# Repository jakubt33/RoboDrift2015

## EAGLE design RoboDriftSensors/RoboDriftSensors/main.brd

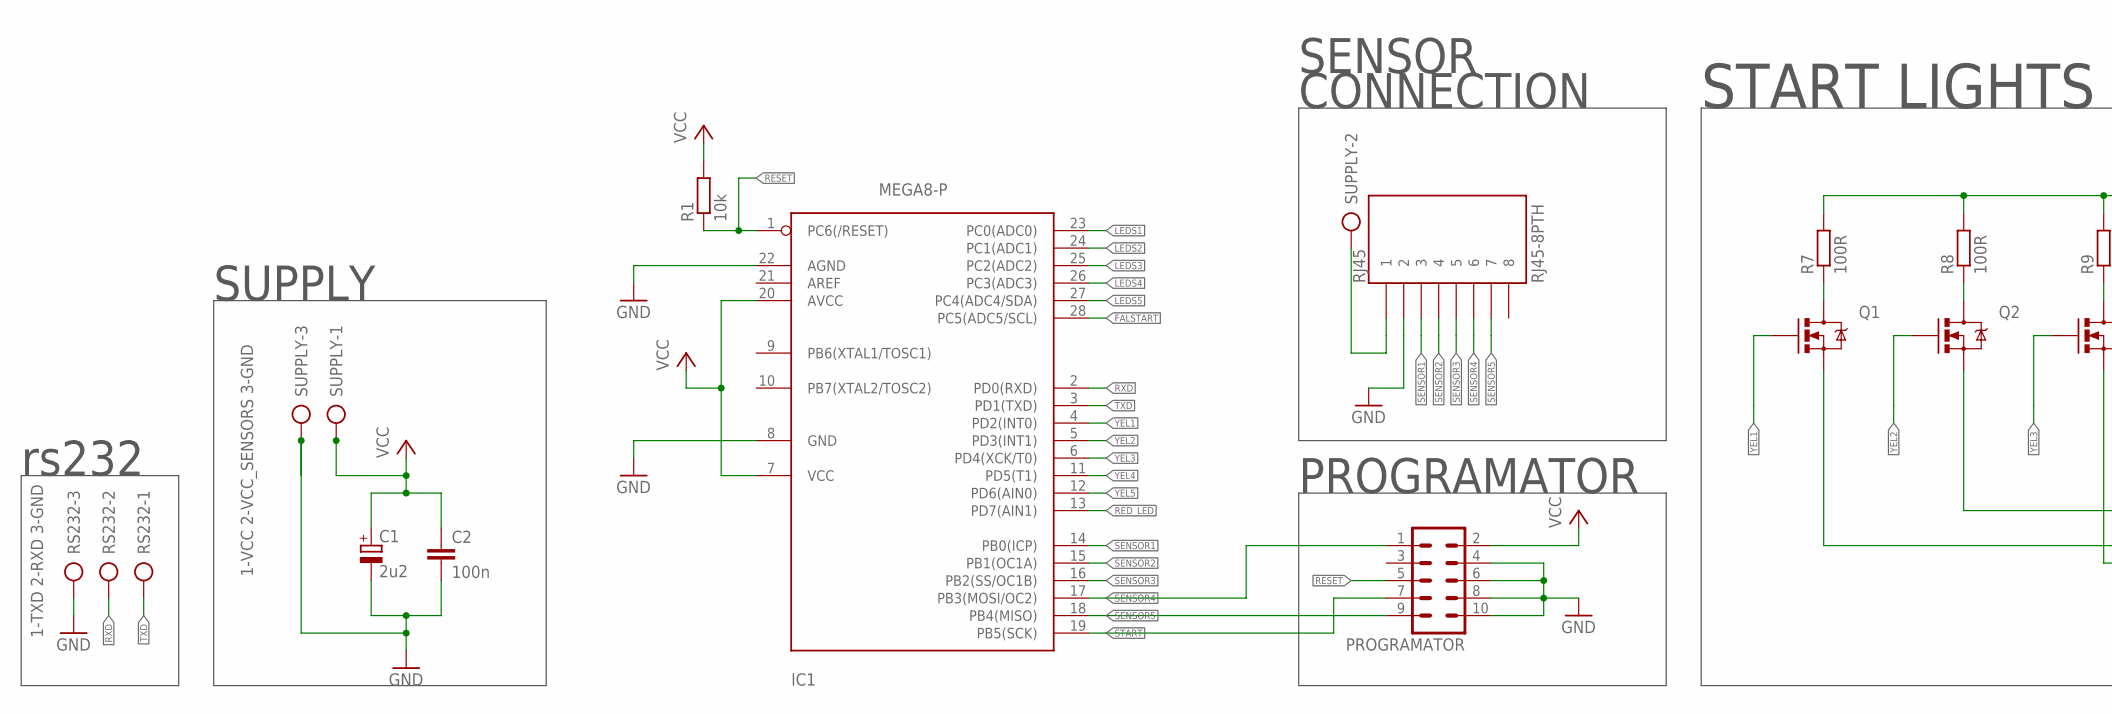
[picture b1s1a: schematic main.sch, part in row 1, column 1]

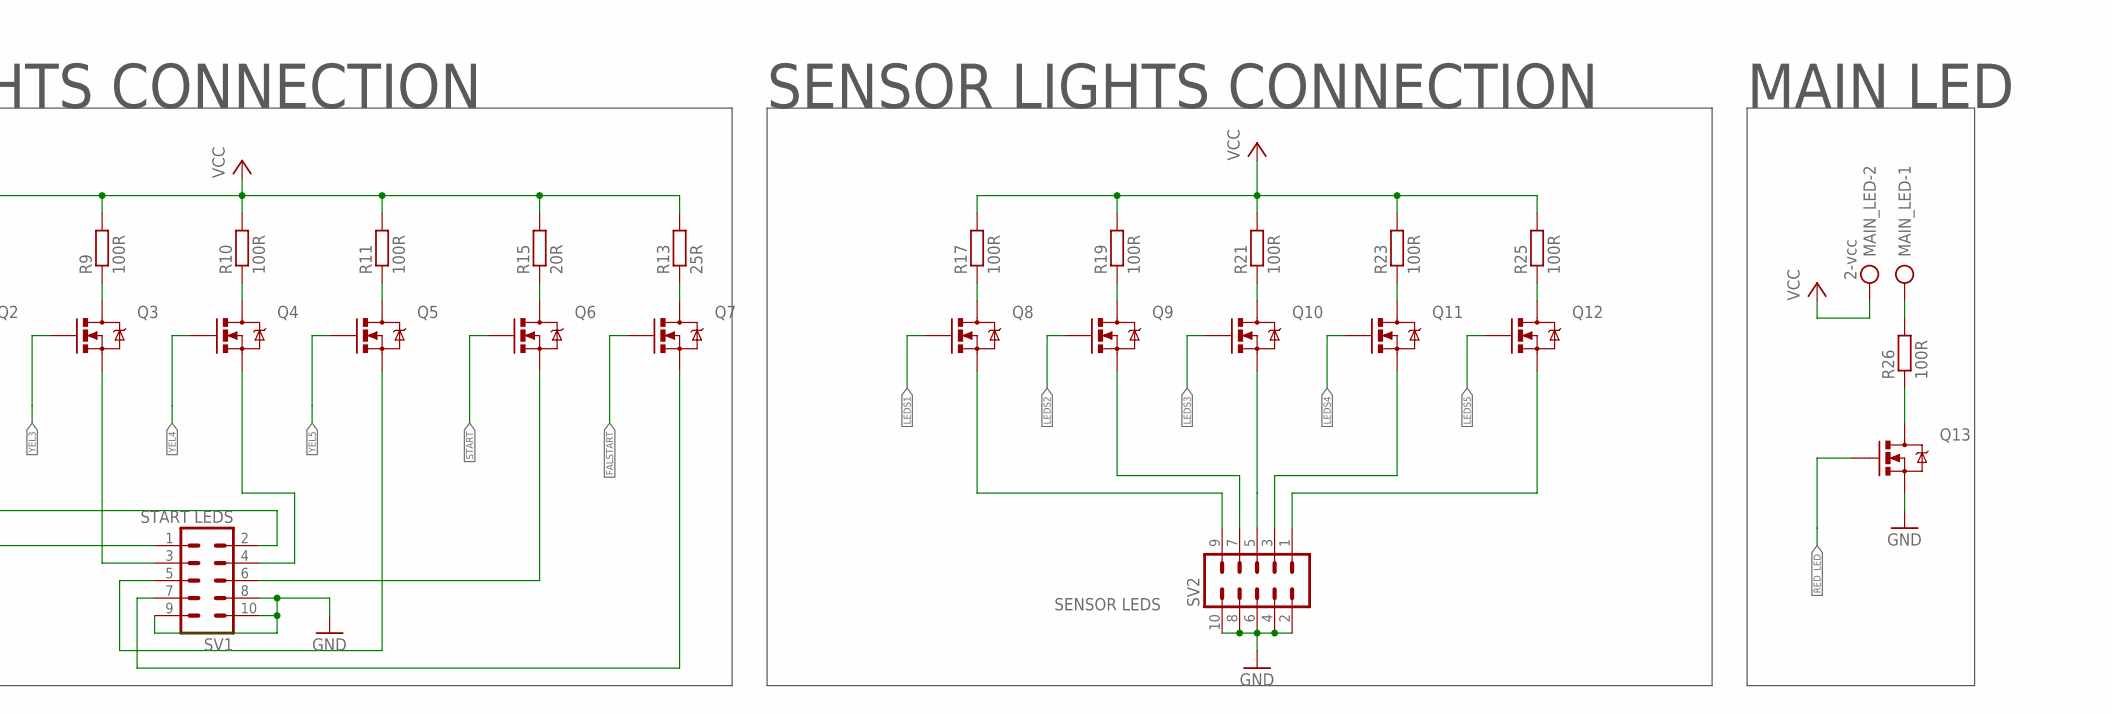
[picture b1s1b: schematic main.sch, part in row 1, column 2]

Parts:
C1: 2u2; E2-5
C2: 100n; C0805
IC1: MEGA8-P; DIL28-3
MAIN_LED: 2-vcc; AK300/2
PROGRAMATOR: ML10L
Q1, Q2, Q3, Q4, Q5, Q6, Q7, Q8, Q9, Q10, Q11, Q12, Q13: MOSFET-NCHANNEL2N7002PW; SOT323
R1: 10k; R0805
R7, R8, R9, R10, R11, R17, R19, R21, R23, R25, R26: 100R; R0805
R13: 25R; R0805
R15: 20R; R0805
RJ45: RJ45-8PTH; RJ45-8
RS232: 1-TXD 2-RXD 3-GND; AK300/3
SUPPLY: 1-VCC 2-VCC_SENSORS 3-GND; AK300/3
SV1: START LEDS; ML10
SV2: SENSOR LEDS; ML10

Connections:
FALSTART: IC1.28 (PC5(ADC5/SCL)), Q7.1 (G)
GND: C1.-, C2.2, IC1.8 (GND), IC1.22 (AGND), PROGRAMATOR.4, PROGRAMATOR.6, PROGRAMATOR.8, PROGRAMATOR.10, Q13.2 (S), RJ45.2, RS232.3, SUPPLY.3, SV1.8, SV1.9, SV1.10, SV2.2, SV2.4, SV2.6, SV2.8, SV2.10
LEDS1: IC1.23 (PC0(ADC0)), Q8.1 (G)
LEDS2: IC1.24 (PC1(ADC1)), Q9.1 (G)
LEDS3: IC1.25 (PC2(ADC2)), Q10.1 (G)
LEDS4: IC1.26 (PC3(ADC3)), Q11.1 (G)
LEDS5: IC1.27 (PC4(ADC4/SDA)), Q12.1 (G)
unnamed: Q1.3 (D), R7.1
unnamed: Q8.2 (S), SV2.9
unnamed: Q2.3 (D), R8.1
unnamed: Q3.3 (D), R9.1
unnamed: Q4.3 (D), R10.1
unnamed: Q5.3 (D), R11.1
unnamed: Q9.2 (S), SV2.7
unnamed: Q11.2 (S), SV2.3
unnamed: Q12.2 (S), SV2.1
unnamed: Q7.3 (D), R13.1
unnamed: Q6.3 (D), R15.1
unnamed: Q8.3 (D), R17.1
unnamed: Q9.3 (D), R19.1
unnamed: Q10.3 (D), R21.1
unnamed: Q11.3 (D), R23.1
unnamed: Q12.3 (D), R25.1
unnamed: Q10.2 (S), SV2.5
unnamed: Q1.2 (S), SV1.1
unnamed: Q2.2 (S), SV1.2
unnamed: Q3.2 (S), SV1.3
unnamed: Q4.2 (S), SV1.4
unnamed: Q5.2 (S), SV1.5
unnamed: Q6.2 (S), SV1.6
unnamed: Q7.2 (S), SV1.7
unnamed: RJ45.1, SUPPLY.2
unnamed: Q13.3 (D), R26.1
unnamed: MAIN_LED.1, R26.2
RED_LED: IC1.13 (PD7(AIN1)), Q13.1 (G)
RESET: IC1.1 (PC6(/RESET)), PROGRAMATOR.5, R1.1
RXD: IC1.2 (PD0(RXD)), RS232.2
SENSOR1: IC1.14 (PB0(ICP)), RJ45.3
SENSOR2: IC1.15 (PB1(OC1A)), RJ45.4
SENSOR3: IC1.16 (PB2(SS/OC1B)), RJ45.5
SENSOR4: IC1.17 (PB3(MOSI/OC2)), PROGRAMATOR.1, RJ45.6
SENSOR5: IC1.18 (PB4(MISO)), PROGRAMATOR.9, RJ45.7
START: IC1.19 (PB5(SCK)), PROGRAMATOR.7, Q6.1 (G)
TXD: IC1.3 (PD1(TXD)), RS232.1
VCC: C1.+, C2.1, IC1.7 (VCC), IC1.20 (AVCC), MAIN_LED.2, PROGRAMATOR.2, R1.2, R7.2, R8.2, R9.2, R10.2, R11.2, R13.2, R15.2, R17.2, R19.2, R21.2, R23.2, R25.2, SUPPLY.1
YEL1: IC1.4 (PD2(INT0)), Q1.1 (G)
YEL2: IC1.5 (PD3(INT1)), Q2.1 (G)
YEL3: IC1.6 (PD4(XCK/T0)), Q3.1 (G)
YEL4: IC1.11 (PD5(T1)), Q4.1 (G)
YEL5: IC1.12 (PD6(AIN0)), Q5.1 (G)

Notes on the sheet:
START LIGHTS CONNECTION
SENSOR LIGHTS CONNECTION
PROGRAMATOR
SUPPLY
rs232
MAIN LED
CONNECTION
SENSOR

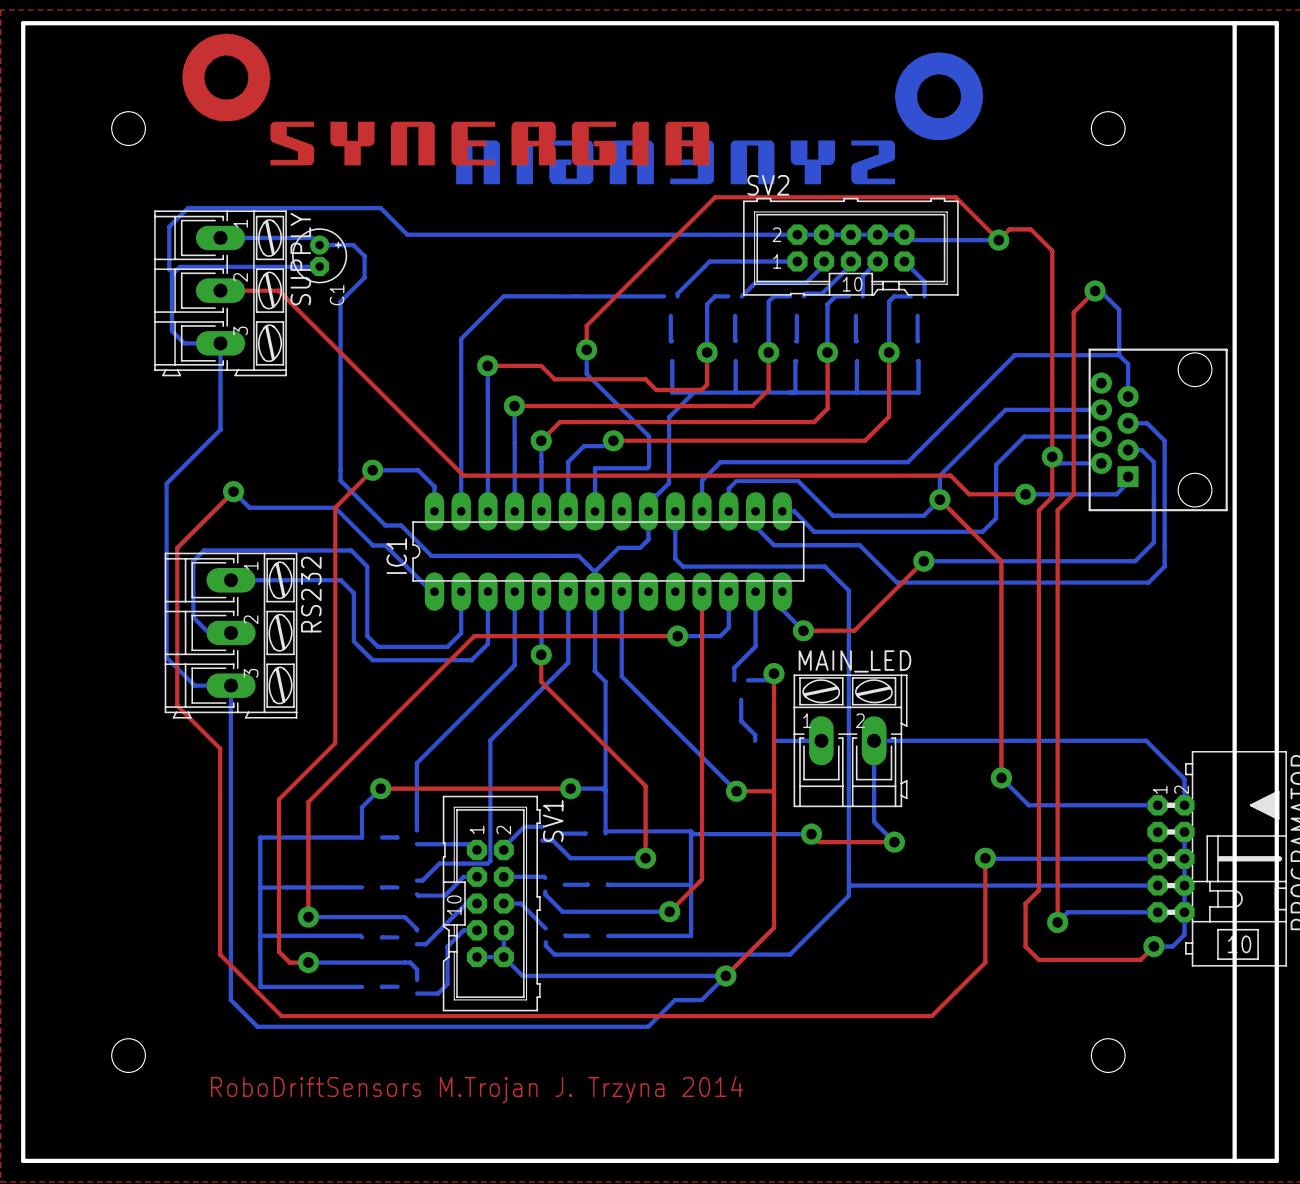
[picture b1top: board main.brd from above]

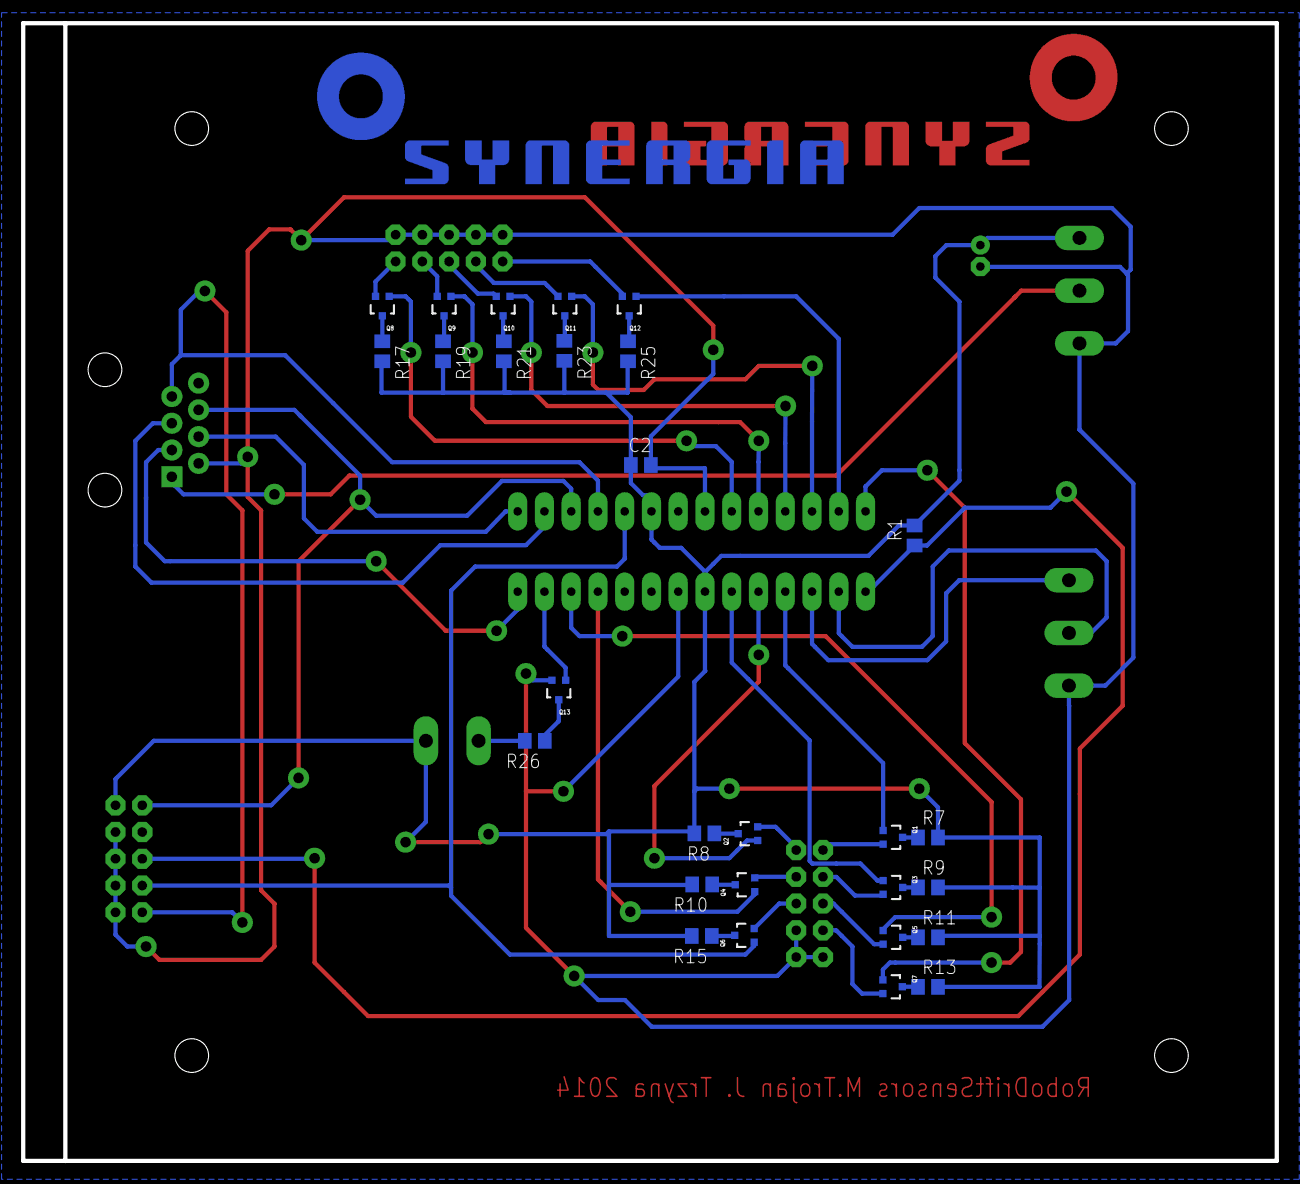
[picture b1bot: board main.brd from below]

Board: 2 copper layers, 119.0 x 108.0 mm, 39 parts (29 on the bottom side), 50 nets.

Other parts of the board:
U$1, U$2: SYNERGIA_50MM

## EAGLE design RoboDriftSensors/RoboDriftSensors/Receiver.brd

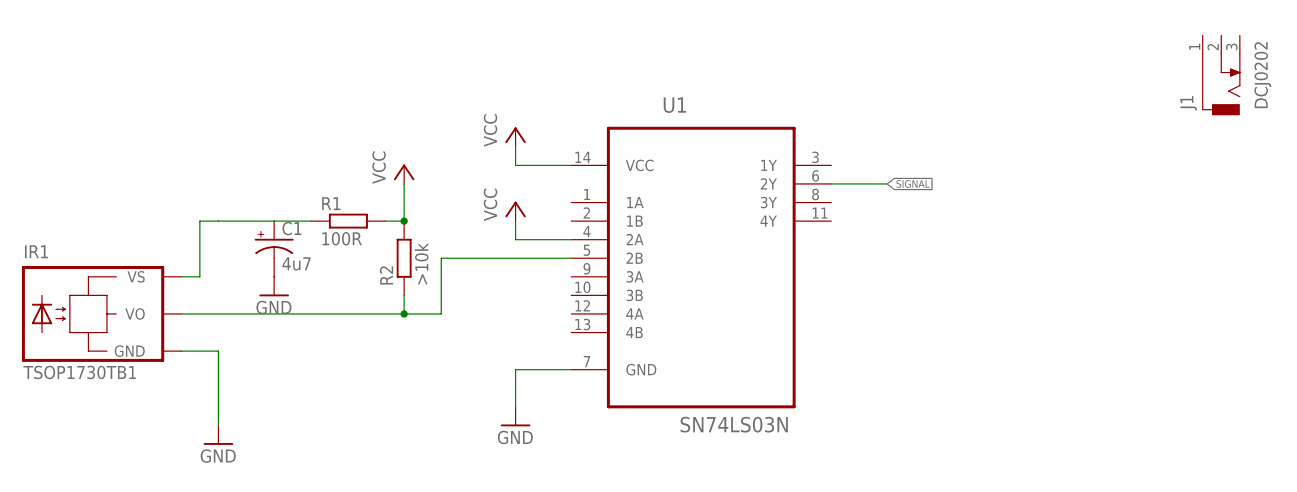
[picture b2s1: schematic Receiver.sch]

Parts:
C1: 4u7; E2-4
IR1: TSOP1730TB1; TSOP17_TB1
J1: DCJ0202
R1: 100R; 0204/5
R2: >10k; 0204/5
U1: SN74LS03N; DIP254P762X508-14

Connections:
GND: C1.-, IR1.GND, U1.7 (GND)
unnamed: IR1.VO, R2.1, U1.5 (2B)
unnamed: C1.+, IR1.VS, R1.1
SIGNAL: U1.6 (2Y)
VCC: R1.2, R2.2, U1.4 (2A), U1.14 (VCC)

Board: 2 copper layers, 6 parts (0 on the bottom side), 4 nets, no tracks yet.

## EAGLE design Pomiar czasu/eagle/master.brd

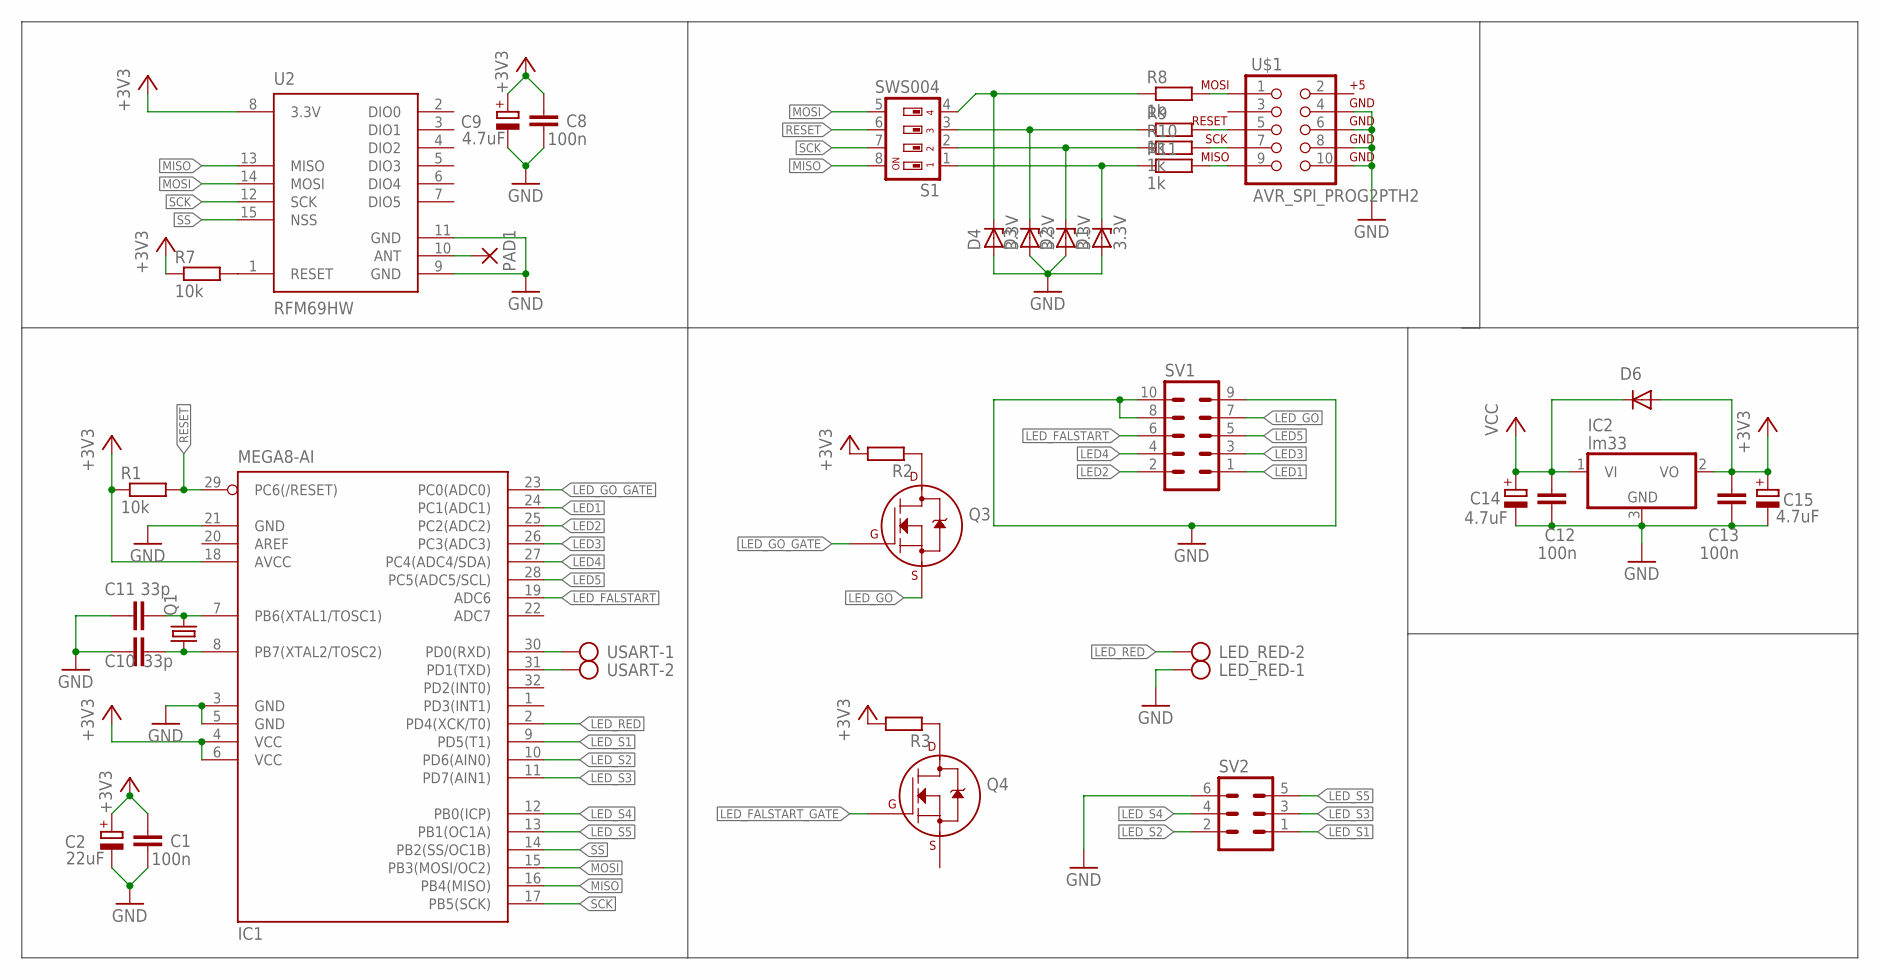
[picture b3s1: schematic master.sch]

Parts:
C1, C8, C12, C13: 100n; C0805
C2: 22uF; E2-5
C9, C14, C15: 4.7uF; E2-5
C10, C11: 33p; C0805
D1, D2, D3, D4: 3.3V; SOD80C
D6: DIODE-DO214AC; DO214AC
IC1: MEGA8-AI; TQFP32-08
IC2: lm33; TO252
LED_RED: AK500/2
PAD1: WIREPADSMD5-2,5; 5-2,5
Q1: CRYSTALHC49UP; HC49UP
Q3, Q4: 2N7000_SOT23; SOT-23
R1, R7: 10k; R0805
R2, R3: R-EU_R0805; R0805
R8, R9, R10, R11: 1k; R0805
S1: SWS004; SMS-004
SV1: ML10
SV2: ML6
U2: RFM69HW; RFM69W-XXXS2
U$1: AVR_SPI_PROG2PTH2; 2X5-SHROUDED
USART: AK500/2

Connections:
+3V3: C1.1, C2.+, C8.1, C9.+, C13.1, C15.+, D6.A, IC1.4 (VCC), IC1.6 (VCC), IC1.18 (AVCC), IC2.2 (VO), R1.1, R2.2, R3.2, R7.1, U2.8 (3.3V)
GND: C1.2, C2.-, C8.2, C9.-, C10.1, C11.1, C12.2, C13.2, C14.-, C15.-, D1.A, D2.A, D3.A, D4.A, IC1.3 (GND), IC1.5 (GND), IC1.21 (GND), IC2.3 (GND), LED_RED.1, SV1.8, SV1.9, SV1.10, SV2.6, U2.9 (GND), U2.11 (GND), U$1.4, U$1.6, U$1.8, U$1.10
LED1: IC1.24 (PC1(ADC1)), SV1.1
LED2: IC1.25 (PC2(ADC2)), SV1.2
LED3: IC1.26 (PC3(ADC3)), SV1.3
LED4: IC1.27 (PC4(ADC4/SDA)), SV1.4
LED5: IC1.28 (PC5(ADC5/SCL)), SV1.5
LED_FALSTART: IC1.19 (ADC6), SV1.6
LED_FALSTART_GATE: Q4.1 (G)
LED_GO: Q3.2 (S), SV1.7
LED_GO_GATE: IC1.23 (PC0(ADC0)), Q3.1 (G)
LED_RED: IC1.2 (PD4(XCK/T0)), LED_RED.2
LED_S1: IC1.9 (PD5(T1)), SV2.1
LED_S2: IC1.10 (PD6(AIN0)), SV2.2
LED_S3: IC1.11 (PD7(AIN1)), SV2.3
LED_S4: IC1.12 (PB0(ICP)), SV2.4
LED_S5: IC1.13 (PB1(OC1A)), SV2.5
MISO: IC1.16 (PB4(MISO)), S1.8, U2.13 (MISO)
MOSI: IC1.15 (PB3(MOSI/OC2)), S1.5, U2.14 (MOSI)
unnamed: Q3.3 (D), R2.1
unnamed: Q4.3 (D), R3.1
unnamed: R7.2, U2.1 (RESET)
unnamed: D4.C, R8.1, S1.4
unnamed: PAD1.1, U2.10 (ANT)
unnamed: D3.C, R9.1, S1.3
unnamed: D2.C, R10.1, S1.2
unnamed: D1.C, R11.1, S1.1
unnamed: R8.2, U$1.1
unnamed: R11.2, U$1.9
unnamed: R10.2, U$1.7
unnamed: R9.2, U$1.5
unnamed: C11.2, IC1.7 (PB6(XTAL1/TOSC1)), Q1.2
unnamed: C10.2, IC1.8 (PB7(XTAL2/TOSC2)), Q1.1
RESET: IC1.29 (PC6(/RESET)), R1.2, S1.6
RXD: IC1.30 (PD0(RXD)), USART.1
SCK: IC1.17 (PB5(SCK)), S1.7, U2.12 (SCK)
SS: IC1.14 (PB2(SS/OC1B)), U2.15 (NSS)
TXD: IC1.31 (PD1(TXD)), USART.2
VCC: C12.1, C14.+, D6.C, IC2.1 (VI)

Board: 2 copper layers, 36 parts (0 on the bottom side), 38 nets, no tracks yet.

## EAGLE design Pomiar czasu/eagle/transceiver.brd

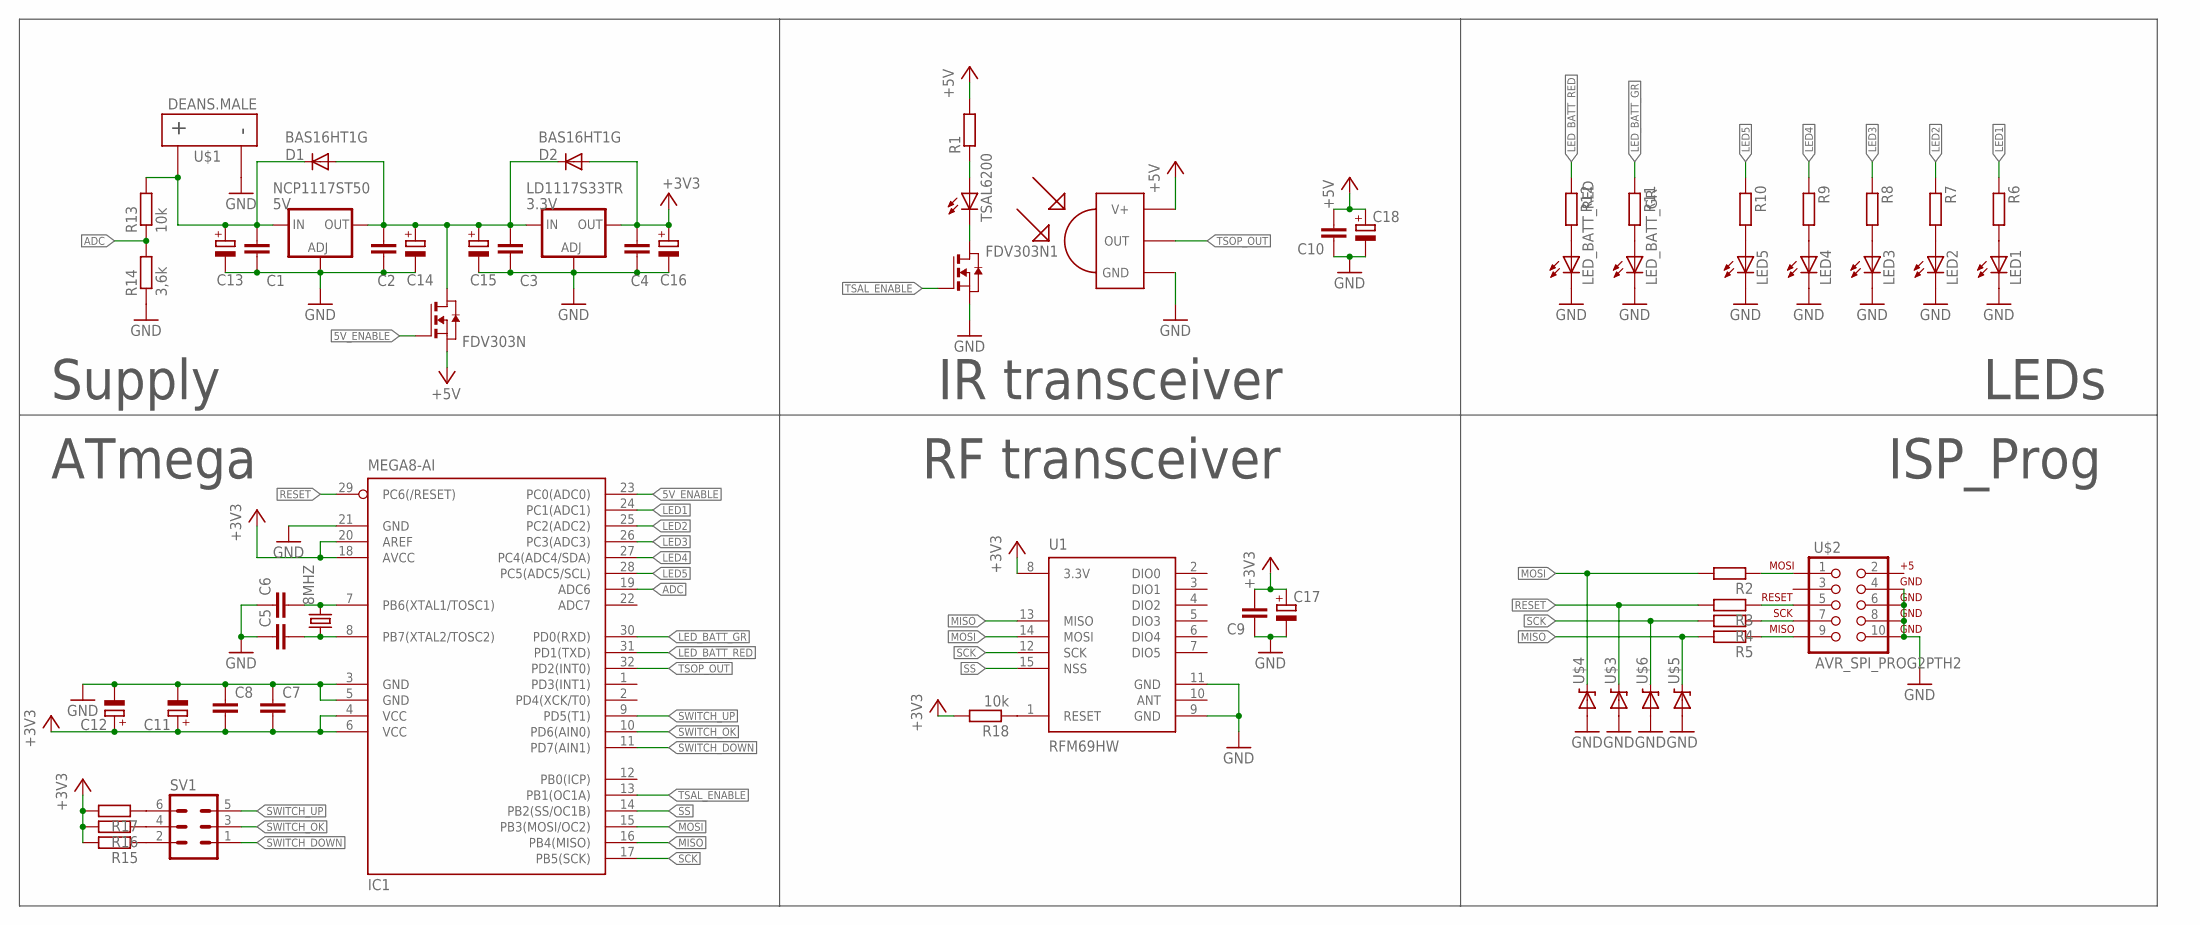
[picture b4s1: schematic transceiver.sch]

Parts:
8MHZ: CRYSTALHC49UP; HC49UP
C1, C2, C3, C4, C5, C6, C7, C8, C9, C10: C-EUC0805; C0805
C11, C12, C13, C14, C15, C16, C17, C18: CPOL-EUE3.5-8; E3,5-8
D1, D2: BAS16HT1G; SOD-323
FDV303N, FDV303N1: NMOSSOT23; SOT-23
IC1: MEGA8-AI; TQFP32-08
LD1117S33TR: 3.3V; SOT223
LED1, LED2, LED3, LED4, LED5: LED5MM
LED_BATT_GR: LED5MM
LED_BATT_RED: LED5MM
NCP1117ST50: 5V; SOT223
R1, R2, R3, R4, R5, R6, R7, R8, R9, R10, R11, R12, R15, R16, R17: R-EU_R0805; R0805
R13, R18: 10k; R0805
R14: 3,6k; R0805
SV1: ML6
TSAL6200: LED5MM
TSOP: TSOP4836; TSOP18XX
U1: RFM69HW; RFM69W-XXXS2
U$1: DEANS.MALE; DEANSM
U$2: AVR_SPI_PROG2PTH2; 2X5-SHROUDED
U$3, U$4, U$5, U$6: DIODE-ZENER-BZT52; SOD-323

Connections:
5V_ENABLE: FDV303N.3 (G), IC1.23 (PC0(ADC0))
+3V3: C4.1, C7.2, C8.2, C9.2, C11.+, C12.+, C16.+, C17.+, D2.2 (A), IC1.4 (VCC), IC1.6 (VCC), IC1.18 (AVCC), IC1.20 (AREF), LD1117S33TR.2 (OUT), R15.2, R16.2, R17.2, R18.2, U1.8 (3.3V)
+5V: C10.2, C18.+, FDV303N.2 (S), R1.2, TSOP.VCC (V+)
ADC: IC1.19 (ADC6), R13.1, R14.2
GND: C1.2, C2.2, C3.2, C4.2, C5.1, C6.1, C7.1, C8.1, C9.1, C10.1, C11.-, C12.-, C13.-, C14.-, C15.-, C16.-, C17.-, C18.-, FDV303N1.2 (S), IC1.3 (GND), IC1.5 (GND), IC1.21 (GND), LD1117S33TR.1 (ADJ), LED1.K (C), LED2.K (C), LED3.K (C), LED4.K (C), LED5.K (C), LED_BATT_GR.K (C), LED_BATT_RED.K (C), NCP1117ST50.1 (ADJ), R14.1, TSOP.GND, U1.9 (GND), U1.11 (GND), U$1.P$NEG, U$2.4, U$2.6, U$2.8, U$2.10, U$3.2 (A), U$4.2 (A), U$5.2 (A), U$6.2 (A)
LED1: IC1.24 (PC1(ADC1)), R6.1
LED2: IC1.25 (PC2(ADC2)), R7.1
LED3: IC1.26 (PC3(ADC3)), R8.1
LED4: IC1.27 (PC4(ADC4/SDA)), R9.1
LED5: IC1.28 (PC5(ADC5/SCL)), R10.1
LED_BATT_GR: IC1.30 (PD0(RXD)), R11.1
LED_BATT_RED: IC1.31 (PD1(TXD)), R12.1
MISO: IC1.16 (PB4(MISO)), R5.2, U1.13 (MISO), U$5.1 (C)
MOSI: IC1.15 (PB3(MOSI/OC2)), R2.2, U1.14 (MOSI), U$4.1 (C)
unnamed: C1.1, C13.+, D1.1 (C), NCP1117ST50.3 (IN), R13.2, U$1.P$POS
unnamed: C2.1, C3.1, C14.+, C15.+, D1.2 (A), D2.1 (C), FDV303N.1 (D), LD1117S33TR.3 (IN), NCP1117ST50.2 (OUT)
unnamed: FDV303N1.1 (D), TSAL6200.K (C)
unnamed: R2.1, U$2.1
unnamed: R3.1, U$2.5
unnamed: R4.1, U$2.7
unnamed: R5.1, U$2.9
unnamed: R1.1, TSAL6200.A
unnamed: LED1.A, R6.2
unnamed: LED2.A, R7.2
unnamed: LED3.A, R8.2
unnamed: LED4.A, R9.2
unnamed: LED5.A, R10.2
unnamed: 8MHZ.2, C6.2, IC1.7 (PB6(XTAL1/TOSC1))
unnamed: 8MHZ.1, C5.2, IC1.8 (PB7(XTAL2/TOSC2))
unnamed: LED_BATT_GR.A, R11.2
unnamed: LED_BATT_RED.A, R12.2
unnamed: R15.1, SV1.2
unnamed: R16.1, SV1.4
unnamed: R17.1, SV1.6
unnamed: R18.1, U1.1 (RESET)
RESET: IC1.29 (PC6(/RESET)), R3.2, U$3.1 (C)
SCK: IC1.17 (PB5(SCK)), R4.2, U1.12 (SCK), U$6.1 (C)
SS: IC1.14 (PB2(SS/OC1B)), U1.15 (NSS)
SWITCH_DOWN: IC1.11 (PD7(AIN1)), SV1.1
SWITCH_OK: IC1.10 (PD6(AIN0)), SV1.3
SWITCH_UP: IC1.9 (PD5(T1)), SV1.5
TSAL_ENABLE: FDV303N1.3 (G), IC1.13 (PB1(OC1A))
TSOP_OUT: IC1.32 (PD2(INT0)), TSOP.OUT

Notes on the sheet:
ATmega
Supply
IR transceiver
RF transceiver
ISP_Prog
LEDs

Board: 2 copper layers, 61 parts (0 on the bottom side), 43 nets, no tracks yet.

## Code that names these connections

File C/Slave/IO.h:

/*
 * main.h
 *
 *  Created on: 7 mar 2015
 *      Author: Kuba
 */

#ifndef IO_H_
#define IO_H_

//------------------------------------
#define DDR_LED DDRC
#define PORT_LED PORTC

#define LED1 PC1
#define LED2 PC2
#define LED3 PC3
#define LED4 PC4
#define LED5 PC5

#define LED1_OFF PORTC &= ~_BV(LED1);
#define LED1_ON PORTC |= _BV(LED1);
#define LED2_OFF PORTC &= ~_BV(LED2);
#define LED2_ON PORTC |= _BV(LED2);
#define LED3_OFF PORTC &= ~_BV(LED3);
#define LED3_ON PORTC |= _BV(LED3);
#define LED4_OFF PORTC &= ~_BV(LED4);
#define LED4_ON PORTC |= _BV(LED4);
#define LED5_OFF PORTC &= ~_BV(LED5);
#define LED5_ON PORTC |= _BV(LED5);
//------------------------------------

//------------------------------------
#define DDR_LED_BATT DDRD

#define LED_BATT_GR PD0
#define LED_BATT_RED PD1

#define LED_BATT_GR_OFF PORTD &= ~_BV(LED_BATT_GR);
#define LED_BATT_GR_ON PORTD |= _BV(LED_BATT_GR);
#define LED_BATT_RED_OFF PORTD &= ~_BV(LED_BATT_RED);
#define LED_BATT_RED_ON PORTD |= _BV(LED_BATT_RED);
//------------------------------------

//------------------------------------
#define DDR_TSAL DDRB
#define DDR_STRIPE DDRB
#define PORT_TSAL PORTB
#define PORT_STRIPE DDRB

#define SWITCH_5V PC0
#define DDR_5V DDRC
#define PORT_5V PORTC

#define TSAL_ENABLE PB1
#define LED_STRIPE PB0

#define TSAL_OFF_CTC    TCCR1A &= ~(1<<COM1A0); //
#define TSAL_OFF_DDR PORT_TSAL &= ~(1<<TSAL_ENABLE);
#define TSAL_ON_CTC     TCCR1A |=  (1<<COM1A0);   //
#define TSAL_ON_DDR  PORT_TSAL |=  (1<<TSAL_ENABLE);
#define LED_STRIPE_OFF PORT_STRIPE &= ~_BV(LED_STRIPE);
#define LED_STRIPE_ON PORT_STRIPE |= _BV(LED_STRIPE);

//------------------------------------

//------------------------------------
#define DDR_SWITCH DDRD
#define PIN_SWITCH PIND

#define SWITCH_UP PD7
#define SWITCH_OK PD6
#define SWITCH_DOWN PD5
//------------------------------------

//------------------------------------
#define DDR_TSOP DDRD
#define PIN_TSOP PIND
#define TSOP PD2
//------------------------------------

//------------------------------------
#define DDR_SPI DDRB
#define PORT_SPI PORTB
#define SS PB2
#define SCK PB5
#define MOSI PB3
#define MISO PB4
#define DIO0 PD3
#define	PORT_DIO PORTD
#define PIN_DIO PIND
#define DDR_DIO DDRD
//------------------------------------

#endif /* IO_H_ */

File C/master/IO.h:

/*
 * IO.h
 *
 *  Created on: 17 mar 2015
 *      Author: Kuba
 */

#ifndef IO_H_
#define IO_H_


//------------------------------------
#define DDR_LED_Y DDRC
#define DDR_LED_GO DDRC
#define PORT_LED_Y PORTC
#define PORT_LED_GO PORTC
#define DDR_LED_RED DDRD
#define PORT_LED_RED PORTD

#define DDR_LED_S35 DDRB
#define DDR_LED_S124 DDRD
#define PORT_LED_S35 PORTB
#define PORT_LED_S124 PORTD

#define DDR_LED_FALSTART DDRD
#define PORT_LED_S PORTD
#define PORT_LED_FALSTART PORTD

#define LED1Y PC3
#define LED2Y PC4
#define LED3Y PC2
#define LED4Y PC5
#define LED5Y PC1
#define LED_GO PC0
#define LED_FALSTART PD3
#define LED_RED PD4

#define LED1S PD5
#define LED2S PD6
#define LED3S PB1
#define LED4S PD7
#define LED5S PB0

#define LED1Y_OFF PORT_LED_Y &= ~_BV(LED1Y);
#define LED1Y_ON PORT_LED_Y |= _BV(LED1Y);
#define LED2Y_OFF PORT_LED_Y &= ~_BV(LED2Y);
#define LED2Y_ON PORT_LED_Y |= _BV(LED2Y);
#define LED3Y_OFF PORT_LED_Y &= ~_BV(LED3Y);
#define LED3Y_ON PORT_LED_Y |= _BV(LED3Y);
#define LED4Y_OFF PORT_LED_Y &= ~_BV(LED4Y);
#define LED4Y_ON PORT_LED_Y |= _BV(LED4Y);
#define LED5Y_OFF PORT_LED_Y &= ~_BV(LED5Y);
#define LED5Y_ON PORT_LED_Y |= _BV(LED5Y);

#define LED1S_OFF PORT_LED_S124 &= ~_BV(LED1S);
#define LED1S_ON PORT_LED_S124 |= _BV(LED1S);
#define LED2S_OFF PORT_LED_S124 &= ~_BV(LED2S);
#define LED2S_ON PORT_LED_S124 |= _BV(LED2S);
#define LED3S_OFF PORT_LED_S35 &= ~_BV(LED3S);
#define LED3S_ON PORT_LED_S35 |= _BV(LED3S);
#define LED4S_OFF PORT_LED_S124 &= ~_BV(LED4S);
#define LED4S_ON PORT_LED_S124 |= _BV(LED4S);
#define LED5S_OFF PORT_LED_S35 &= ~_BV(LED5S);
#define LED5S_ON PORT_LED_S35 |= _BV(LED5S);

#define LED_RED_OFF PORT_LED_RED &= ~_BV(LED_RED);
#define LED_RED_ON PORT_LED_RED |= _BV(LED_RED);

#define LED_GO_OFF PORT_LED_GO &= ~_BV(LED_GO);
#define LED_GO_ON PORT_LED_GO |= _BV(LED_GO);
#define LED_FALSTART_OFF PORT_LED_FALSTART &= ~_BV(LED_FALSTART);
#define LED_FALSTART_ON PORT_LED_FALSTART |= _BV(LED_FALSTART);
//------------------------------------

//------------------------------------
#define DDR_SPI DDRB
#define PORT_SPI PORTB
#define SS PB2
#define SCK PB5
#define MOSI PB3
#define MISO PB4

#define PORT_DIO PORTD
#define DDR_DIO DDRD
#define PIN_DIO PIND
#define DIO0 PD2
#endif /* IO_H_ */

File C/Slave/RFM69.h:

// **********************************************************************************
// Driver definition for HopeRF RFM69W/RFM69HW/RFM69CW/RFM69HCW, Semtech SX1231/1231H
// **********************************************************************************
// Copyright Felix Rusu (2014), felix@lowpowerlab.com
// http://lowpowerlab.com/
// **********************************************************************************
// License
// **********************************************************************************
// This program is free software; you can redistribute it 
// and/or modify it under the terms of the GNU General    
// Public License as published by the Free Software       
// Foundation; either version 3 of the License, or        
// (at your option) any later version.                    
//                                                        
// This program is distributed in the hope that it will   
// be useful, but WITHOUT ANY WARRANTY; without even the  
// implied warranty of MERCHANTABILITY or FITNESS FOR A   
// PARTICULAR PURPOSE. See the GNU General Public        
// License for more details.                              
//                                                        
// You should have received a copy of the GNU General    
// Public License along with this program.
// If not, see <http://www.gnu.org/licenses/>.
//                                                        
// Licence can be viewed at                               
// http://www.gnu.org/licenses/gpl-3.0.txt
//
// Please maintain this license information along with authorship
// and copyright notices in any redistribution of this code
// **********************************************************************************
#ifndef RFM69_h
#define RFM69_h

#define RF69_MAX_DATA_LEN       61 // to take advantage of the built in AES/CRC we want to limit the frame size to the internal FIFO size (66 bytes - 3 bytes overhead - 2 bytes crc)
#define RF69_SPI_CS             SS // SS is the SPI slave select pin, for instance D10 on ATmega328


#define CSMA_LIMIT              -90 // upper RX signal sensitivity threshold in dBm for carrier sense access
#define RF69_MODE_SLEEP         0 // XTAL OFF
#define RF69_MODE_STANDBY       1 // XTAL ON
#define RF69_MODE_SYNTH         2 // PLL ON
#define RF69_MODE_RX            3 // RX MODE
#define RF69_MODE_TX            4 // TX MODE

// available frequency bands
#define RF69_315MHZ            31 // non trivial values to avoid misconfiguration
#define RF69_433MHZ            43
#define RF69_868MHZ            86
#define RF69_915MHZ            91

#define KEY         "Robo_Drift_2015"
#define MASTER      50
#define NETWORKID   100
#define GATEWAYID   1
#define FREQUENCY   RF69_433MHZ //Match this with the version of your Moteino! (others: RF69_433MHZ, RF69_868MHZ)
#define SENSOR1 	51 //non trivial numbers
#define SENSOR2 	52
#define SENSOR3 	53
#define SENSOR4 	54
#define SENSOR5 	55
#define isRFM69HW	true
#define isMASTER	false



#define false				  0
#define true				  1
#define null                  0
#define COURSE_TEMP_COEF    -90 // puts the temperature reading in the ballpark, user can fine tune the returned value
#define RF69_BROADCAST_ADDR 255
#define RF69_CSMA_LIMIT_MS 1000
#define RF69_TX_LIMIT_MS   1000
//#define RF69_FSTEP  61.03515625 // == FXOSC / 2^19 = 32MHz / 2^19 (p13 in datasheet)

volatile uint8_t myAddress;
volatile uint8_t dataReceived;
volatile uint8_t mode; // should be protected?
volatile uint8_t slaveSelectPin;
volatile uint8_t interruptPin;
volatile uint8_t interruptNum;
volatile uint8_t promiscuousMode;
volatile uint8_t powerLevel;
volatile unsigned char DATA[RF69_MAX_DATA_LEN]; // recv/xmit buf, including header & crc bytes
volatile uint8_t DATALEN;
volatile uint8_t SENDERID;
volatile uint8_t TARGETID; // should match _address
volatile uint8_t PAYLOADLEN;
volatile uint8_t ACK_REQUESTED;
volatile uint8_t ACK_RECEIVED; // should be polled immediately after sending a packet with ACK request
//volatile int16_t RSSI; // most accurate RSSI during reception (closest to the reception)


void setAddress(uint8_t addr);
void setNetwork(uint8_t networkID);
uint8_t canSend();
void send(uint8_t toAddress, const void* buffer, uint8_t bufferSize, uint8_t requestACK);
uint8_t sendWithRetry(uint8_t toAddress, char buffer, uint8_t bufferSize, uint8_t retries); // 40ms roundtrip req for 61byte packets
uint8_t receiveDone(uint8_t fromNodeID);
uint8_t ACKReceived(uint8_t fromNodeID);
//uint8_t ACKRequested();
//void sendACK(const void* buffer, uint8_t bufferSize);
//uint32_t getFrequency();
//void setFrequency(uint32_t freqHz);
void encrypt(const char* key);
//void setCS(uint8_t newSPISlaveSelect);
//int16_t readRSSI(/*uint8_t forceTrigger*/);
void promiscuous(uint8_t onOff);
void setHighPower(uint8_t onOFF); // has to be called after initialize() for RFM69HW
void setPowerLevel(uint8_t level); // reduce/increase transmit power level
void sleep();
//uint8_t readTemperature(uint8_t calFactor); // get CMOS temperature (8bit)
//void rcCalibration(); // calibrate the internal RC oscillator for use in wide temperature variations - see datasheet section [4.3.5. RC Timer Accuracy]

// allow hacking registers by making these public
uint8_t readReg(uint8_t addr);
void writeReg(uint8_t addr, uint8_t val);
void readAllRegs();


//static void isr0();
//void virtual interruptHandler();
void sendFrame(uint8_t toAddress, char buffer, uint8_t bufferSize, uint8_t requestACK, uint8_t sendACK);
uint8_t init_RFM69();
void receiveBegin();
void setMode(uint8_t mode);
void setHighPowerRegs(uint8_t onOff);
void select();
void unselect();

#endif

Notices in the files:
parts and their libraries:
SparkFun-RF: Licensing: Creative Commons ShareAlike 4.0 International - https://creativecommons.org/licenses/by-sa/4.0
SparkFun: Licensing: CC v3.0 Share-Alike You are welcome to use this library for commercial purposes.
